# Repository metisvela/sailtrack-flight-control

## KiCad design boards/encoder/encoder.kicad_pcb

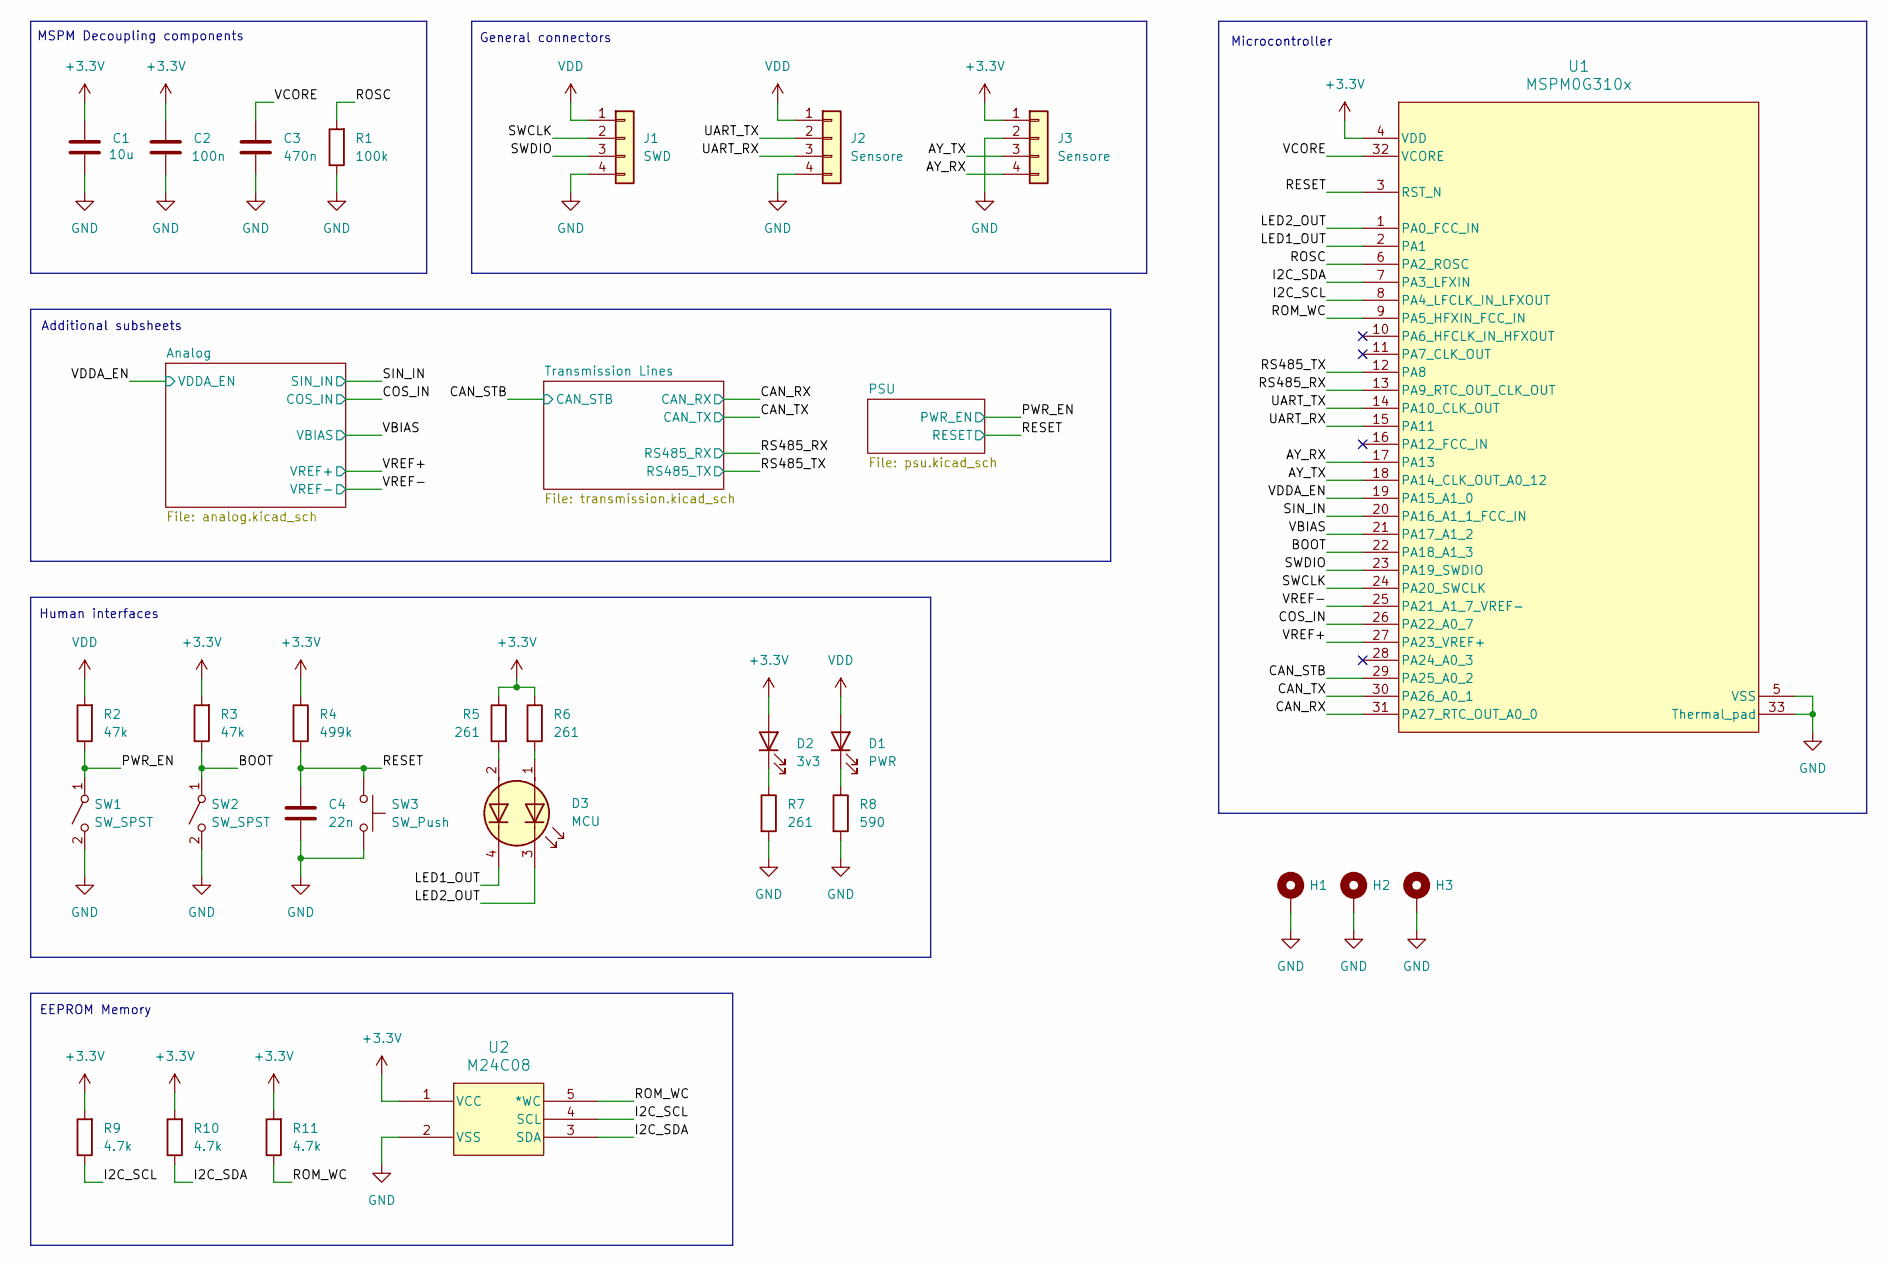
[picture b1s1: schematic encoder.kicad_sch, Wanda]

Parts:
C1: 10u; C_0603_1608Metric
C2: 100n; C_0603_1608Metric
C3: 470n; C_0603_1608Metric
C4: 22n; C_0603_1608Metric
D1: PWR; LED_0603_1608Metric
D2: 3v3; LED_0603_1608Metric
D3: MCU; LED_0606_1615Metric
H1, H2, H3: MountingHole; MountingHole_3.2mm_M3_DIN965_Pad
J1: SWD; JST_XH_B4B-XH-A_1x04_P2.50mm_Vertical
J2, J3: Sensore; JST_XH_B4B-XH-A_1x04_P2.50mm_Vertical
R1: 100k; R_0603_1608Metric
R2, R3: 47k; R_0603_1608Metric
R4: 499k; R_0603_1608Metric
R5, R6, R7: 261; R_0603_1608Metric
R8: 590; R_0603_1608Metric
R9, R10, R11: 4.7k; R_0603_1608Metric
SW1, SW2: SW_SPST; SW_DS04-254-1-01BK-SMT
SW3: SW_Push; SW_TS04-66-65-BK-260-SMT
U1: MSPM0G310x; Texas_RHB0032E_VQFN-32-1EP_5x5mm_P0.5mm_EP3.45x3.45mm_Therm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
U2: M24C08; UFDFPN5_1P7X1P4_STM

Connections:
+3.3V: C1.1, C2.1, D2.2 (A), J3.1, R3.2, R4.1, R5.1, R6.1, R9.2, R10.2, R11.2, U1.4 (VDD), U2.1 (VCC); also elsewhere on the board
/AY_RX: J3.4, U1.17 (PA13)
/AY_TX: J3.3, U1.18 (PA14_CLK_OUT_A0_12)
/BOOT: R3.1, SW2.1 (A), U1.22 (PA18_A1_3)
/CAN_RX: U1.31 (PA27_RTC_OUT_A0_0); also elsewhere on the board
/CAN_STB: U1.29 (PA25_A0_2); also elsewhere on the board
/CAN_TX: U1.30 (PA26_A0_1); also elsewhere on the board
/COS_IN: U1.26 (PA22_A0_7); also elsewhere on the board
/I2C_SCL: R9.1, U1.8 (PA4_LFCLK_IN_LFXOUT), U2.4 (SCL)
/I2C_SDA: R10.1, U1.7 (PA3_LFXIN), U2.3 (SDA)
/LED1_OUT: D3.4 (K2), U1.2 (PA1)
/LED2_OUT: D3.3 (K1), U1.1 (PA0_FCC_IN)
/PWR_EN: R2.1, SW1.1 (A); also elsewhere on the board
/RESET: C4.1, R4.2, SW3.1, U1.3 (RST_N); also elsewhere on the board
/ROM_WC: R11.1, U1.9 (PA5_HFXIN_FCC_IN), U2.5 (*WC)
/ROSC: R1.2, U1.6 (PA2_ROSC)
/RS485_RX: U1.13 (PA9_RTC_OUT_CLK_OUT); also elsewhere on the board
/RS485_TX: U1.12 (PA8); also elsewhere on the board
/SIN_IN: U1.20 (PA16_A1_1_FCC_IN); also elsewhere on the board
/SWCLK: J1.2, U1.24 (PA20_SWCLK)
/SWDIO: J1.3, U1.23 (PA19_SWDIO)
/UART_RX: J2.3, U1.15 (PA11)
/UART_TX: J2.2, U1.14 (PA10_CLK_OUT)
/VBIAS: U1.21 (PA17_A1_2); also elsewhere on the board
/VCORE: C3.1, U1.32 (VCORE)
/VDDA_EN: U1.19 (PA15_A1_0); also elsewhere on the board
/VREF+: U1.27 (PA23_VREF+); also elsewhere on the board
GND: C1.2, C2.2, C3.2, C4.2, H1.1 (1_1), H2.1 (1_1), H3.1 (1_1), J1.4, J2.4, J3.2, R1.1, R7.2, R8.2, SW1.2 (B), SW2.2 (B), SW3.2, U1.5 (VSS), U1.33 (Thermal_pad), U2.2 (VSS); also elsewhere on the board
GNDA: U1.25 (PA21_A1_7_VREF-); also elsewhere on the board
unnamed: D1.1 (K), R8.1
unnamed: D2.1 (K), R7.1
unnamed: D3.1 (A1), R6.2
unnamed: D3.2 (A2), R5.2
VDD: D1.2 (A), J1.1, J2.1, R2.2; also elsewhere on the board

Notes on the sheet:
Additional subsheets
MSPM Decoupling components
General connectors
EEPROM Memory
Microcontroller
Human interfaces

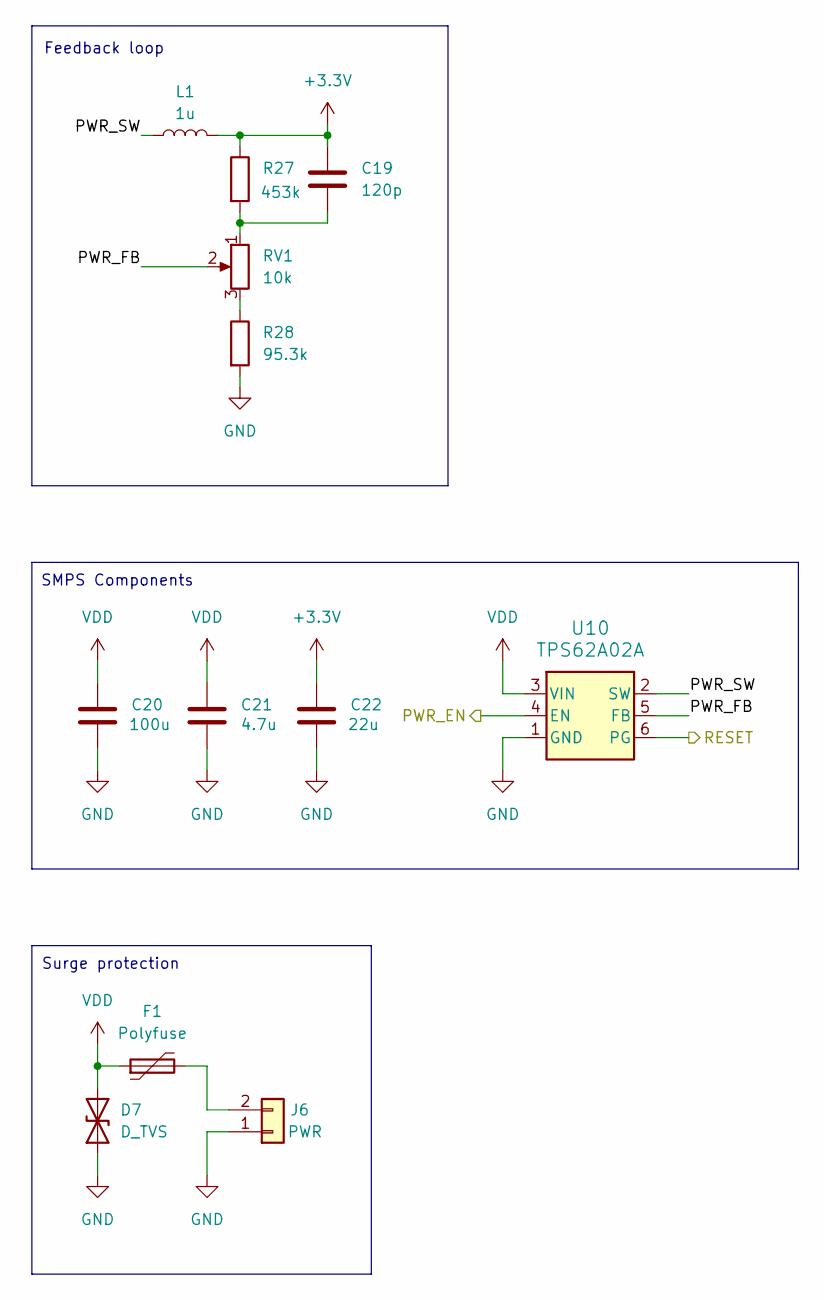
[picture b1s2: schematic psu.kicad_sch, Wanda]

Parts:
C19: 120p; C_0603_1608Metric
C20: 100u; C_1206_3216Metric
C21: 4.7u; C_0603_1608Metric
C22: 22u; C_1206_3216Metric
D7: D_TVS; D_SOD-523
F1: Polyfuse; Fuse_1206_3216Metric
J6: PWR; JST_XH_B2B-XH-A_1x02_P2.50mm_Vertical
L1: 1u; L_1210_3225Metric
R27: 453k; R_0603_1608Metric
R28: 95.3k; R_0603_1608Metric
RV1: 10k; Potentiometer_Bourns_TC33X_Vertical
U10: TPS62A02A; SOT6_DRL_TEX

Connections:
+3.3V: C19.1, C22.1, L1.2, R27.1; also elsewhere on the board
/PSU/PWR_FB: RV1.2, U10.5 (FB)
/PSU/PWR_SW: L1.1, U10.2 (SW)
/PWR_EN: U10.4 (EN); also elsewhere on the board
/RESET: U10.6 (PG); also elsewhere on the board
GND: C20.2, C21.2, C22.2, D7.1 (A1), J6.1, R28.2, U10.1 (GND); also elsewhere on the board
unnamed: C19.2, R27.2, RV1.1
unnamed: F1.2, J6.2
unnamed: R28.1, RV1.3
VDD: C20.1, C21.1, D7.2 (A2), F1.1, U10.3 (VIN); also elsewhere on the board

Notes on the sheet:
Feedback loop
SMPS Components
Surge protection

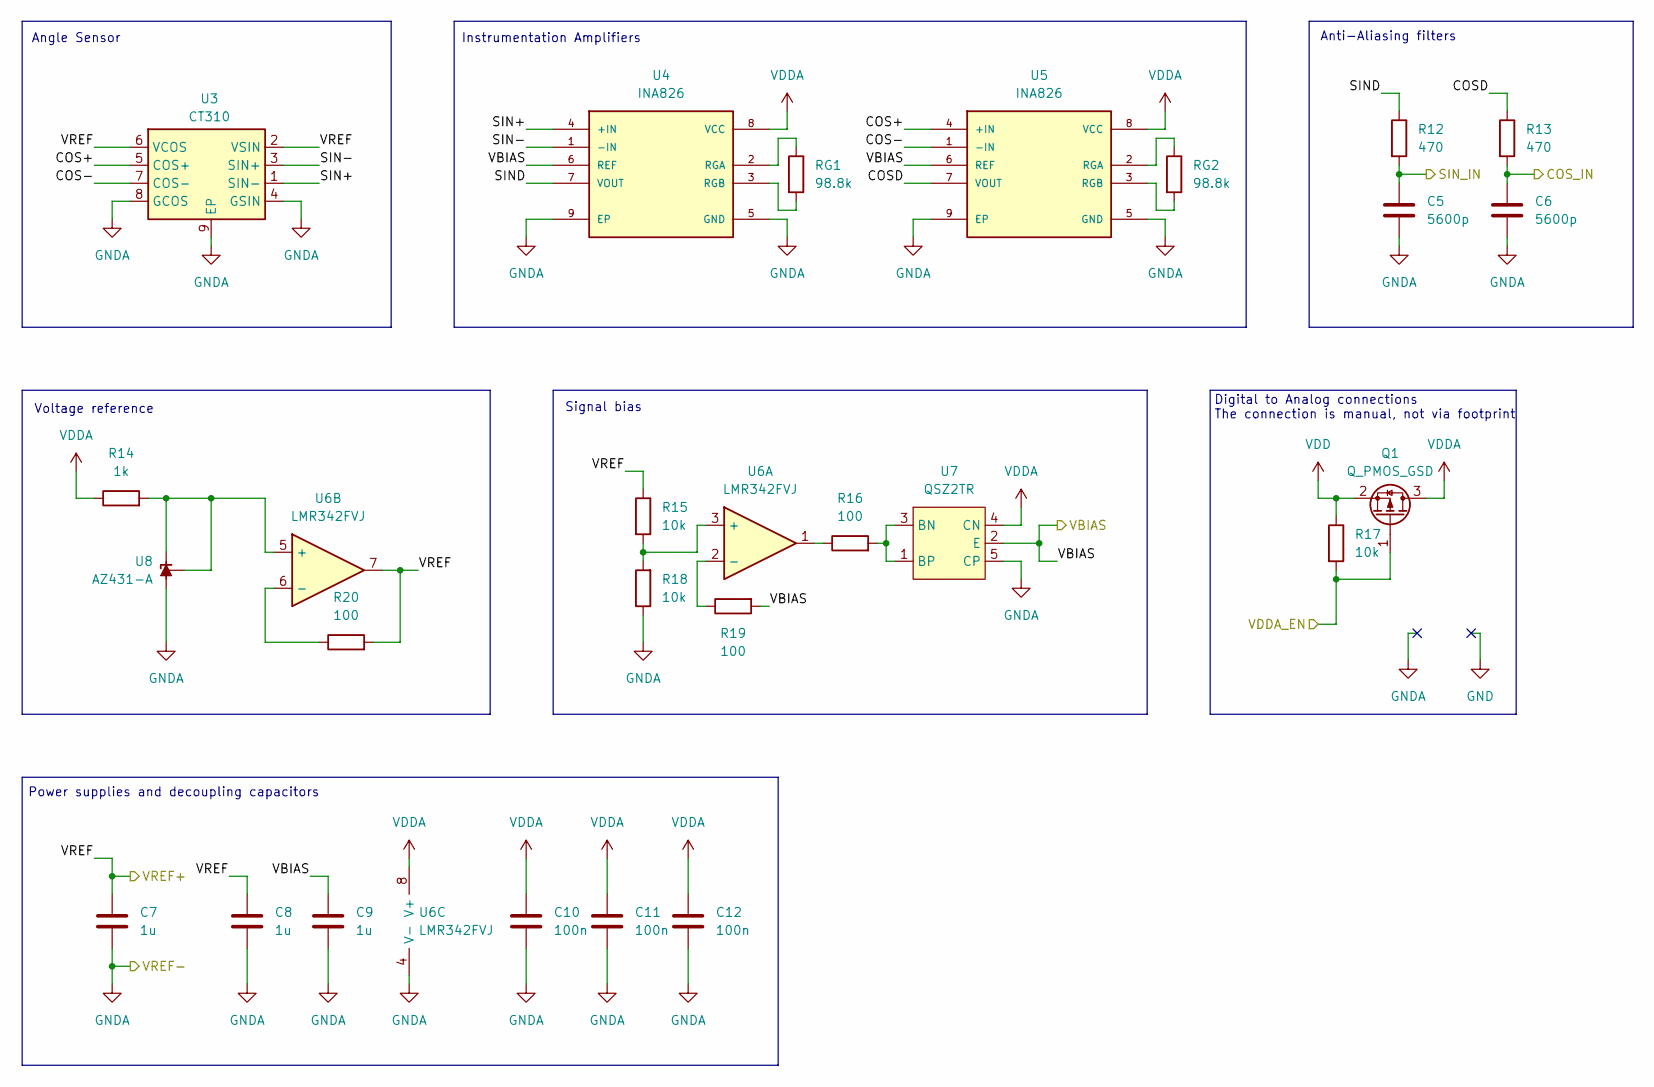
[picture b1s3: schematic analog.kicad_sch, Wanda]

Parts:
C5, C6: 5600p; C_0603_1608Metric
C7, C8, C9: 1u; C_0603_1608Metric
C10, C11, C12: 100n; C_0603_1608Metric
Q1: Q_PMOS_GSD; SOT-23
R12, R13: 470; R_0603_1608Metric
R14: 1k; R_0603_1608Metric
R15, R17, R18: 10k; R_0603_1608Metric
R16, R19, R20: 100; R_0603_1608Metric
RG1, RG2: 98.8k; R_0603_1608Metric
U3: CT310; DFN-8-1EP_2x2mm_P0.5mm_EP0.8x1.6mm
U4, U5: INA826; SON50P300X300X80-9N200X120; PARTREV E
U6: LMR342FVJ; TSSOP-8_3x3mm_P0.65mm
U7: QSZ2TR; TSOT-23-5
U8: AZ431-A; SOT-23-3

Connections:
/Analog/COS+: U3.5 (COS+), U5.4 (+IN)
/Analog/COS-: U3.7 (COS-), U5.1 (-IN)
/Analog/COSD: R13.1, U5.7 (VOUT)
/Analog/SIN+: U3.1 (SIN-), U4.4 (+IN)
/Analog/SIN-: U3.3 (SIN+), U4.1 (-IN)
/Analog/SIND: R12.1, U4.7 (VOUT)
/COS_IN: C6.1, R13.2; also elsewhere on the board
/SIN_IN: C5.1, R12.2; also elsewhere on the board
/VBIAS: C9.2, R19.2, U4.6 (REF), U5.6 (REF), U7.2 (E); also elsewhere on the board
/VDDA_EN: Q1.1 (G), R17.2; also elsewhere on the board
/VREF+: C7.1, C8.2, R15.1, R20.2, U3.2 (VSIN), U3.6 (VCOS), U6.7; also elsewhere on the board
GNDA: C5.2, C6.2, C7.2, C8.1, C9.1, C10.2, C11.2, C12.2, R18.1, U3.4 (GSIN), U3.8 (GCOS), U3.9 (EP), U4.5 (GND), U4.9 (EP), U5.5 (GND), U5.9 (EP), U6.4 (V-), U7.5 (CP), U8.3 (A); also elsewhere on the board
unnamed: R16.1, U6.1
unnamed: RG1.1, U4.2 (RGA)
unnamed: RG1.2, U4.3 (RGB)
unnamed: RG2.1, U5.2 (RGA)
unnamed: RG2.2, U5.3 (RGB)
unnamed: R15.2, R18.2, U6.3 (+)
unnamed: R19.1, U6.2 (-)
unnamed: R14.2, U6.5 (+), U8.1 (REF), U8.2 (K)
unnamed: R20.1, U6.6 (-)
unnamed: R16.2, U7.1 (BP), U7.3 (BN)
VDD: Q1.2 (S), R17.1; also elsewhere on the board
VDDA: C10.1, C11.1, C12.1, Q1.3 (D), R14.1, U4.8 (VCC), U5.8 (VCC), U6.8 (V+), U7.4 (CN)

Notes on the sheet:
Voltage reference
Anti-Aliasing filters
Digital to Analog connections The connection is manual, not via footprint
Instrumentation Amplifiers
Angle Sensor
Power supplies and decoupling capacitors
Signal bias

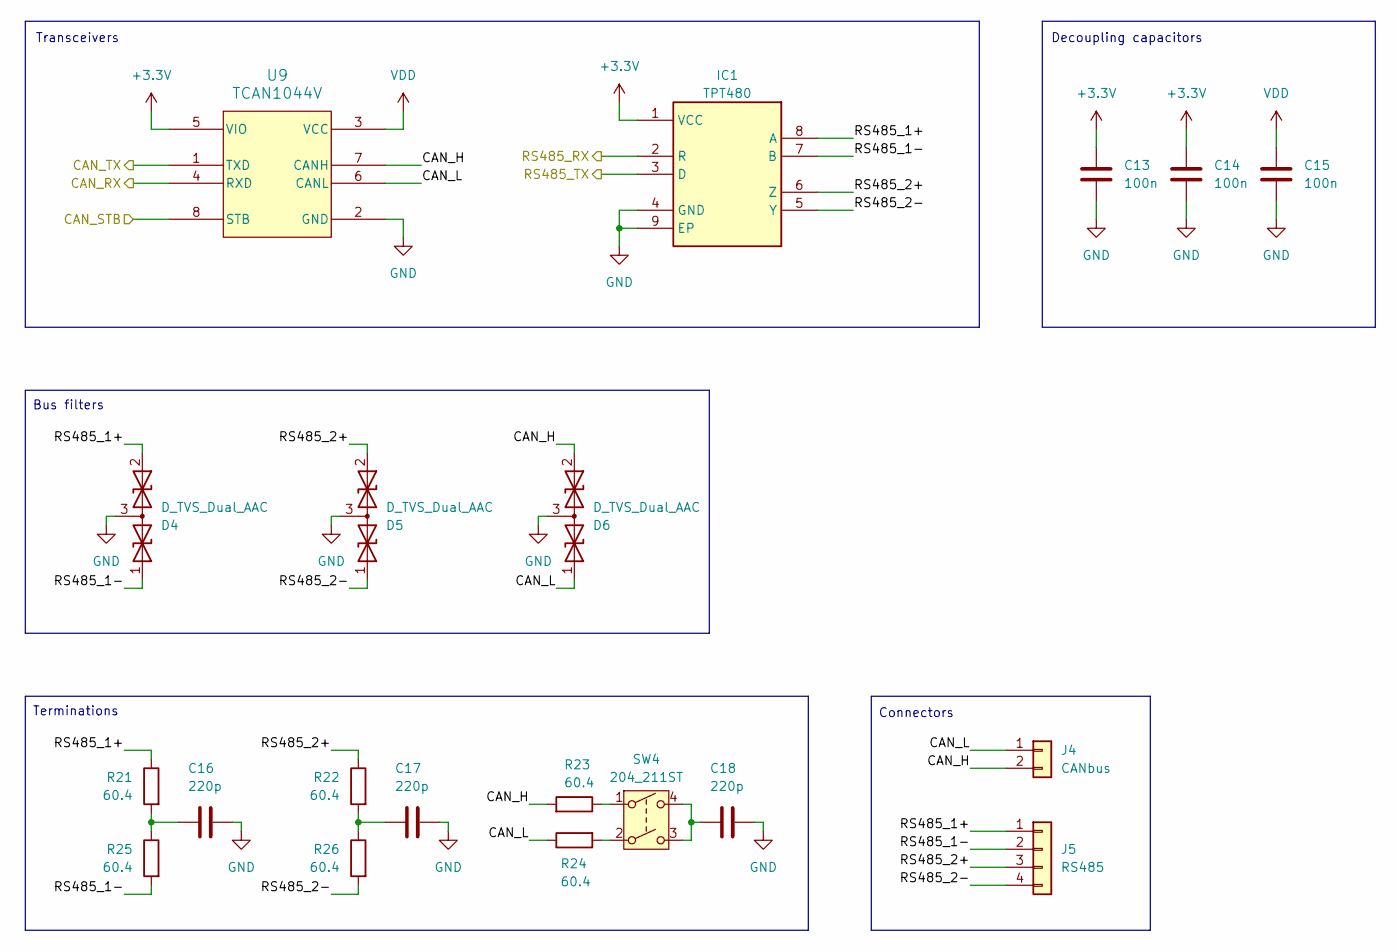
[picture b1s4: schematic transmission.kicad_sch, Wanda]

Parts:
C13, C14, C15: 100n; C_0603_1608Metric
C16, C17, C18: 220p; C_0603_1608Metric
D4, D5, D6: D_TVS_Dual_AAC; SOT-23-3
IC1: TPT480; SON65P300X300X80-9N-D; Manufacturer_Part_Number TPT480-DF6R
J4: CANbus; JST_XH_B2B-XH-A_1x02_P2.50mm_Vertical
J5: RS485; JST_XH_B4B-XH-A_1x04_P2.50mm_Vertical
R21, R22, R23, R24, R25, R26: 60.4; R_0603_1608Metric
SW4: 204_211ST; SW4_204-211ST_CTS
U9: TCAN1044V; SOT-23-THIN-8_DDF_TEX

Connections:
+3.3V: C13.1, C14.1, IC1.1 (VCC), U9.5 (VIO); also elsewhere on the board
/CAN_RX: U9.4 (RXD); also elsewhere on the board
/CAN_STB: U9.8 (STB); also elsewhere on the board
/CAN_TX: U9.1 (TXD); also elsewhere on the board
/RS485_RX: IC1.2 (R); also elsewhere on the board
/RS485_TX: IC1.3 (D); also elsewhere on the board
/Transmission Lines/CAN_H: D6.2 (A2), J4.2, R23.2, U9.7 (CANH)
/Transmission Lines/CAN_L: D6.1 (A1), J4.1, R24.1, U9.6 (CANL)
/Transmission Lines/RS485_1+: D4.2 (A2), IC1.8 (A), J5.1, R21.1
/Transmission Lines/RS485_1-: D4.1 (A1), IC1.7 (B), J5.2, R25.2
/Transmission Lines/RS485_2+: D5.2 (A2), IC1.6 (Z), J5.3, R22.1
/Transmission Lines/RS485_2-: D5.1 (A1), IC1.5 (Y), J5.4, R26.2
GND: C13.2, C14.2, C15.2, C16.1, C17.1, C18.1, D4.3 (common), D5.3 (common), D6.3 (common), IC1.4 (GND), IC1.9 (EP), U9.2 (GND); also elsewhere on the board
unnamed: C16.2, R21.2, R25.1
unnamed: C17.2, R22.2, R26.1
unnamed: R24.2, SW4.2 (1)
unnamed: C18.2, SW4.3 (2), SW4.4
unnamed: R23.1, SW4.1 (3)
VDD: C15.1, U9.3 (VCC); also elsewhere on the board

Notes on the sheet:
Bus filters
Connectors
Decoupling capacitors
Terminations
Transceivers

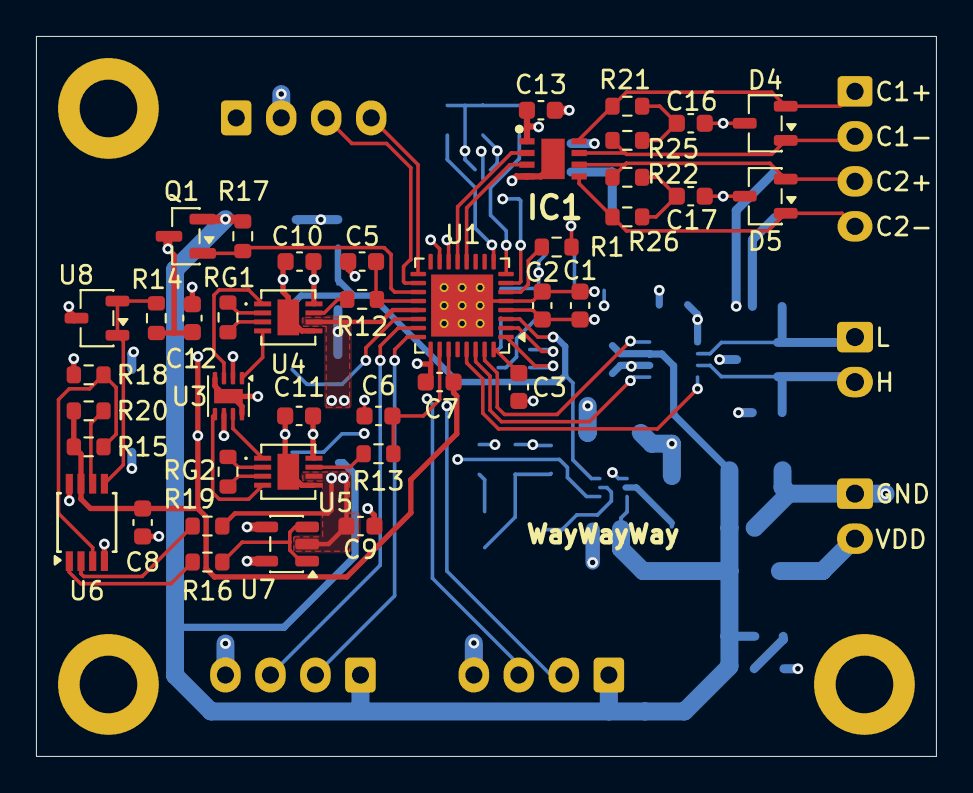
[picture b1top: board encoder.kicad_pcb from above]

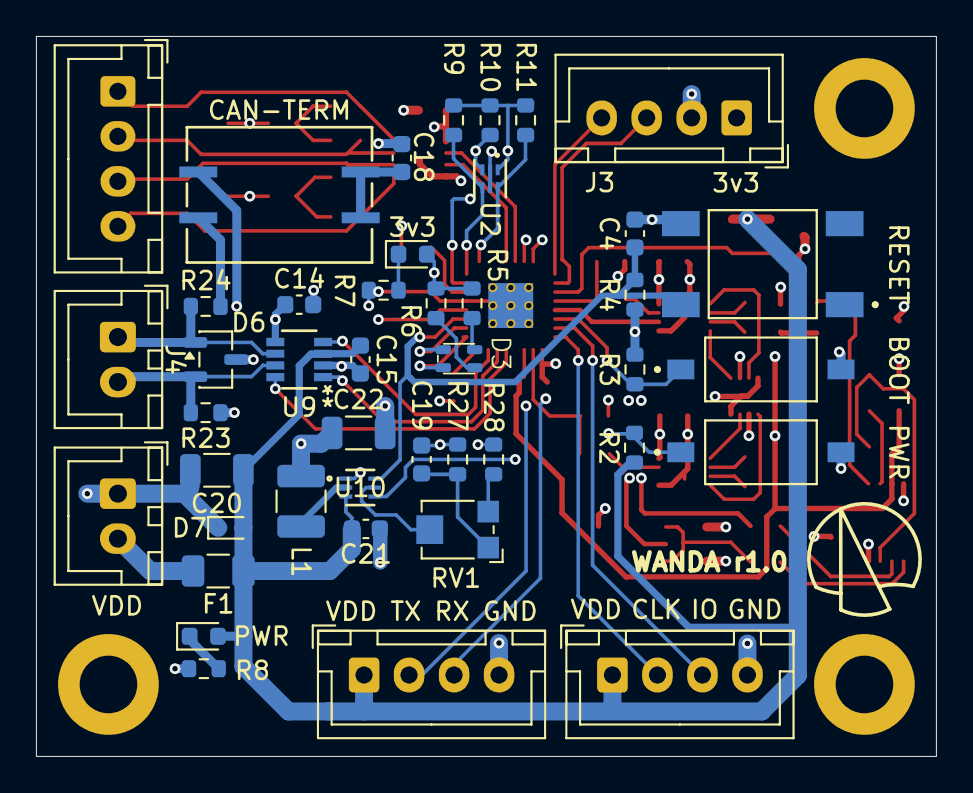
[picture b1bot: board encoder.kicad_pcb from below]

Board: 4 copper layers, 50.0 x 40.0 mm, 87 parts (43 on the bottom side), 67 nets.

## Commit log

2024-05-10 Workspace setup
2024-05-18 Add GitHub workflow
2024-05-18 Minor refactor
2024-12-06 add cam function calculator
2024-12-06 First implementation ultrasonic PID controller
2024-12-20 Add docs directory; add AS5600 datasheet
2024-12-20 Add link to an example project
2025-02-05 AS5600 Sensor manager
2025-02-05 Servo Motor Controller
2025-02-05 Add TransferFunction Class
2025-02-05 step works on cam reversing
2025-02-05 rename apply->evaluate and made code clearer
2025-02-05 add python script to find function from points
2025-02-05 Add pics of cam
2025-02-05 Motor Controller improvement
2025-02-05 Reduce max degree
2025-02-05 First main implementation
2025-02-12 Debug and AS56000 reeding improvement
2025-03-21 Make data easier to understand
2025-03-21 add option to control vertical length
2025-03-21 Motor attachment
2025-03-21 separete code for autotuning and pid
2025-11-01 Moved to framework espidf
2025-11-20 Fixed C linking
2026-03-01 Created encoder kicad project
2026-03-02 Added MSPM0G310x component
2026-03-02 Added TPS62A02A component
2026-03-02 Added build folder to gitignore
2026-03-02 v0.1
2026-03-02 v0.1.1
2026-03-02 v0.1.2
2026-03-02 v0.1.3
2026-03-06 Added IA model
2026-03-06 Replaced IA model
2026-03-07 v0.1.4
2026-03-07 v0.1.5
2026-03-07 Removed backups and lock
2026-03-07 Ignores backups and locks
2026-03-07 v0.1.6
2026-03-07 v0.1.7
2026-03-08 v0.1.8
2026-03-08 Added 2nd indication LED
2026-03-08 v0.1.9
2026-03-08 Added auto saves to ignored files
2026-03-08 v0.1.10
2026-03-08 Added analog sub sheet
2026-03-08 Fixed labels mismatch
2026-03-08 v0.1.11
2026-03-08 v0.1.12
2026-03-08 Added second decoupling capacitor
2026-03-08 v0.1.13
2026-03-08 Added TPT480 component
2026-03-08 Moved busses to external sheet
2026-03-08 Fixed merge conflicts
2026-03-08 Updated gitignore to remove local caches
2026-03-09 v0.1.14
2026-03-09 v0.1.15
2026-03-09 v0.1.16
2026-03-09 Added EEPROM component
2026-03-09 Added EEPROM
2026-03-09 Fixed merge
2026-03-09 v0.1.17
2026-03-09 v0.1.18
2026-03-10 v0.1.19
2026-03-10 Fixed some values
2026-03-10 v0.2.1
2026-03-10 v0.2.2
2026-03-11 Metis-Vela footprint library
2026-03-11 Updated caching files
2026-03-11 v0.2.3
2026-03-11 v0.2.4
2026-03-13 v0.2.5
2026-03-14 v0.2.6
2026-03-15 v0.2.7
2026-03-16 v0.2.8
2026-03-16 v0.2.9
2026-03-16 v0.2.10
2026-03-16 v0.3.0
2026-03-16 v0.3.1
2026-03-18 v0.3.2
2026-03-18 v.0.3.3
2026-03-18 v0.3.4
2026-03-18 v0.3.5
2026-03-18 v0.3.6
2026-03-19 v0.3.7
2026-03-19 v0.3.8
2026-03-19 Fixed the PCB color
2026-03-19 v0.3.9
2026-03-22 v0.3.10
2026-03-25 v0.3.11
2026-03-28 v1.0.0
2026-04-28 v1.0.1
2026-05-04 Fixed ERC errors
2026-05-09 v1.0.2
